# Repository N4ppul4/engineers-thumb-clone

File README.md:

# engineers-thumb-clone
Compression guitar pedal clone

Just my take on the popular compression pedal, its designed to use with perfboard.
This is not in any means verified or anything so take it with a grain of salt.
Program used for schematics and pcb layout is KiCad

Dont know much about copyrights so I assume its same as original design

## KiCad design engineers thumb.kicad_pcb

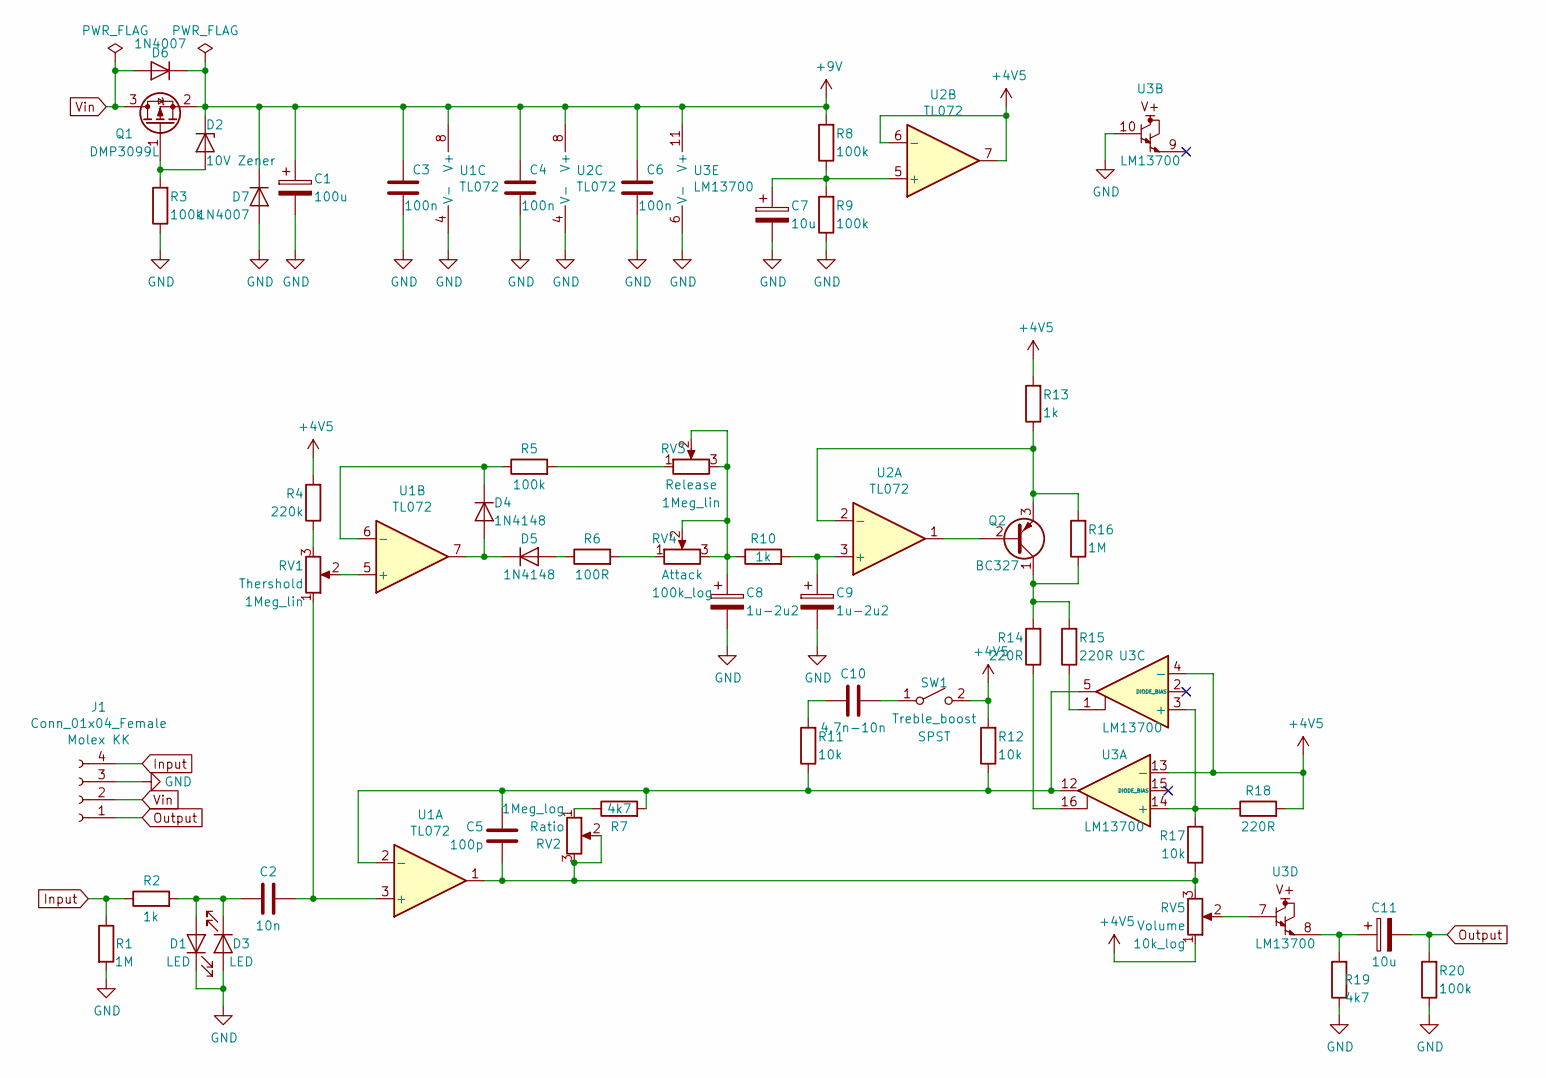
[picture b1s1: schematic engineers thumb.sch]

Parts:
C1: 100u; CP_Radial_D6.3mm_P2.50mm
C2: 10n; C_Box_P5.08mm
C3, C4, C6: 100n; C_Box_P5.08mm
C5: 100p; C_Disc_P2.50mm
C7, C11: 10u; CP_Radial_D6.3mm_P2.50mm
C8, C9: 1u-2u2; CP_Radial_D6.3mm_P2.50mm
C10: 4.7n-10n; C_Box_P5.08mm
D1, D3: LED; LED_D3.0mm
D2: 10V Zener; D_DO-35_SOD27_P7.62mm_Horizontal
D4, D5: 1N4148; D_DO-35_SOD27_P7.62mm_Horizontal
D6, D7: 1N4007; D_DO-35_SOD27_P7.62mm_Horizontal
J1: Conn_01x04_Female; Molex_KK-254_01x04_P2.54mm_Right_Angle
Q1: DMP3099L; SOT-23W_Handsoldering
Q2: BC327; TO-92_Inline_Wide
R1, R16: 1M; R_Axial_DIN0204_L3.6mm_D1.6mm_P7.62mm_Horizontal
R2, R10, R13: 1k; R_Axial_DIN0204_L3.6mm_D1.6mm_P7.62mm_Horizontal
R3, R5, R8, R9, R20: 100k; R_Axial_DIN0204_L3.6mm_D1.6mm_P7.62mm_Horizontal
R4: 220k; R_Axial_DIN0204_L3.6mm_D1.6mm_P7.62mm_Horizontal
R6: 100R; R_Axial_DIN0204_L3.6mm_D1.6mm_P7.62mm_Horizontal
R7, R19: 4k7; R_Axial_DIN0204_L3.6mm_D1.6mm_P7.62mm_Horizontal
R11, R12, R17: 10k; R_Axial_DIN0204_L3.6mm_D1.6mm_P7.62mm_Horizontal
R14, R15, R18: 220R; R_Axial_DIN0204_L3.6mm_D1.6mm_P7.62mm_Horizontal
RV1, RV3: 1Meg_lin; Alpha_16mm_potentiometer
RV2: 1Meg_log; Alpha_16mm_potentiometer
RV4: 100k_log; Alpha_16mm_potentiometer
RV5: 10k_log; Alpha_16mm_potentiometer
SW1: SPST; PinSocket_2x01_P2.54mm_Vertical_Wide
U1, U2: TL072; DIP-8_Socket
U3: LM13700; DIP-16_Socket

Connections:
+4V5: R4.2, R12.2, R13.2, R18.2, RV5.1, SW1.2 (B), U2.6 (-), U2.7, U3.4 (-), U3.13 (-)
+9V: C1.1, C3.1, C4.1, C6.1, D2.1 (K), D6.1 (K), D7.1 (K), Q1.2 (S), R8.2, U1.8 (V+), U2.8 (V+), U3.11 (V+)
GND: C1.2, C3.2, C4.2, C6.2, C7.2, C8.2, C9.2, D1.1 (K), D3.2 (A), D7.2 (A), J1.3, R1.2, R3.1, R9.1, R19.1, R20.1, U1.4 (V-), U2.4 (V-), U3.6 (V-), U3.10
Input: J1.4, R1.1, R2.1
unnamed: C2.1, RV1.1, U1.3 (+)
unnamed: C2.2, D1.2 (A), D3.1 (K), R2.2
unnamed: C5.1, R7.2, R11.1, R12.1, U1.2 (-), U3.5, U3.12
unnamed: C5.2, R17.1, RV2.2, RV2.3, RV5.3, U1.1
unnamed: C7.1, R8.1, R9.2, U2.5 (+)
unnamed: C8.1, R10.1, RV3.2, RV3.3, RV4.2, RV4.3
unnamed: C9.1, R10.2, U2.3 (+)
unnamed: C10.1, SW1.1 (A)
unnamed: C10.2, R11.2
unnamed: C11.1, R19.2, U3.8
unnamed: D2.2 (A), Q1.1 (G), R3.2
unnamed: D4.1 (K), R5.1, U1.6 (-)
unnamed: D4.2 (A), D5.1 (K), U1.7
unnamed: D5.2 (A), R6.1
unnamed: Q2.1 (C), R14.2, R15.2, R16.1
unnamed: Q2.2 (B), U2.1
unnamed: Q2.3 (E), R13.1, R16.2, U2.2 (-)
unnamed: R4.1, RV1.3
unnamed: R5.2, RV3.1
unnamed: R6.2, RV4.1
unnamed: R7.1, RV2.1
unnamed: R14.1, U3.16
unnamed: R15.1, U3.1
unnamed: R17.2, R18.1, U3.3 (+), U3.14 (+)
unnamed: RV1.2, U1.5 (+)
unnamed: RV5.2, U3.7
Output: C11.2, J1.1, R20.2
Vin: D6.2 (A), J1.2, Q1.3 (D)

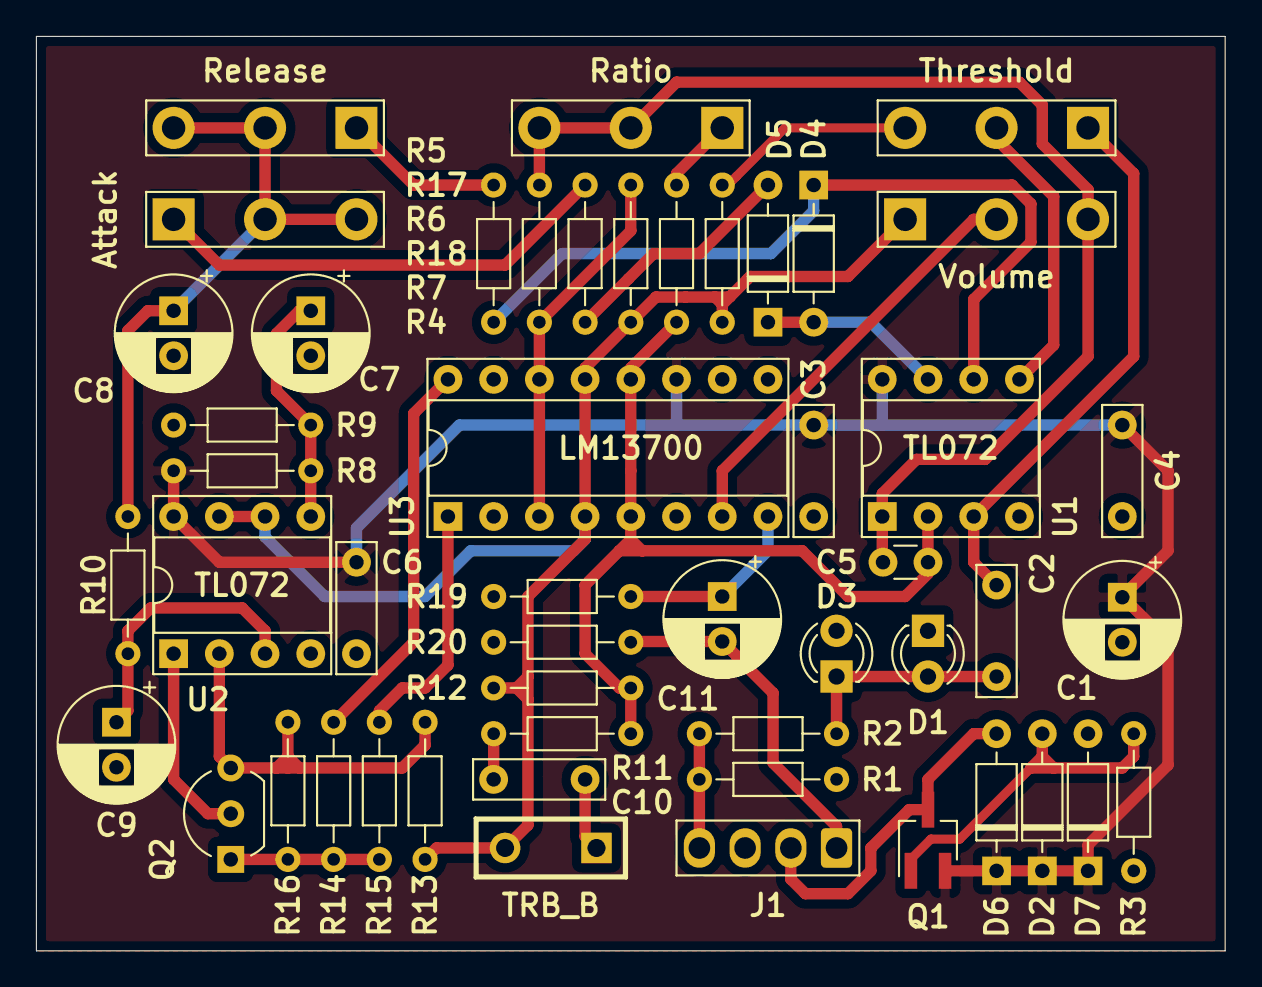
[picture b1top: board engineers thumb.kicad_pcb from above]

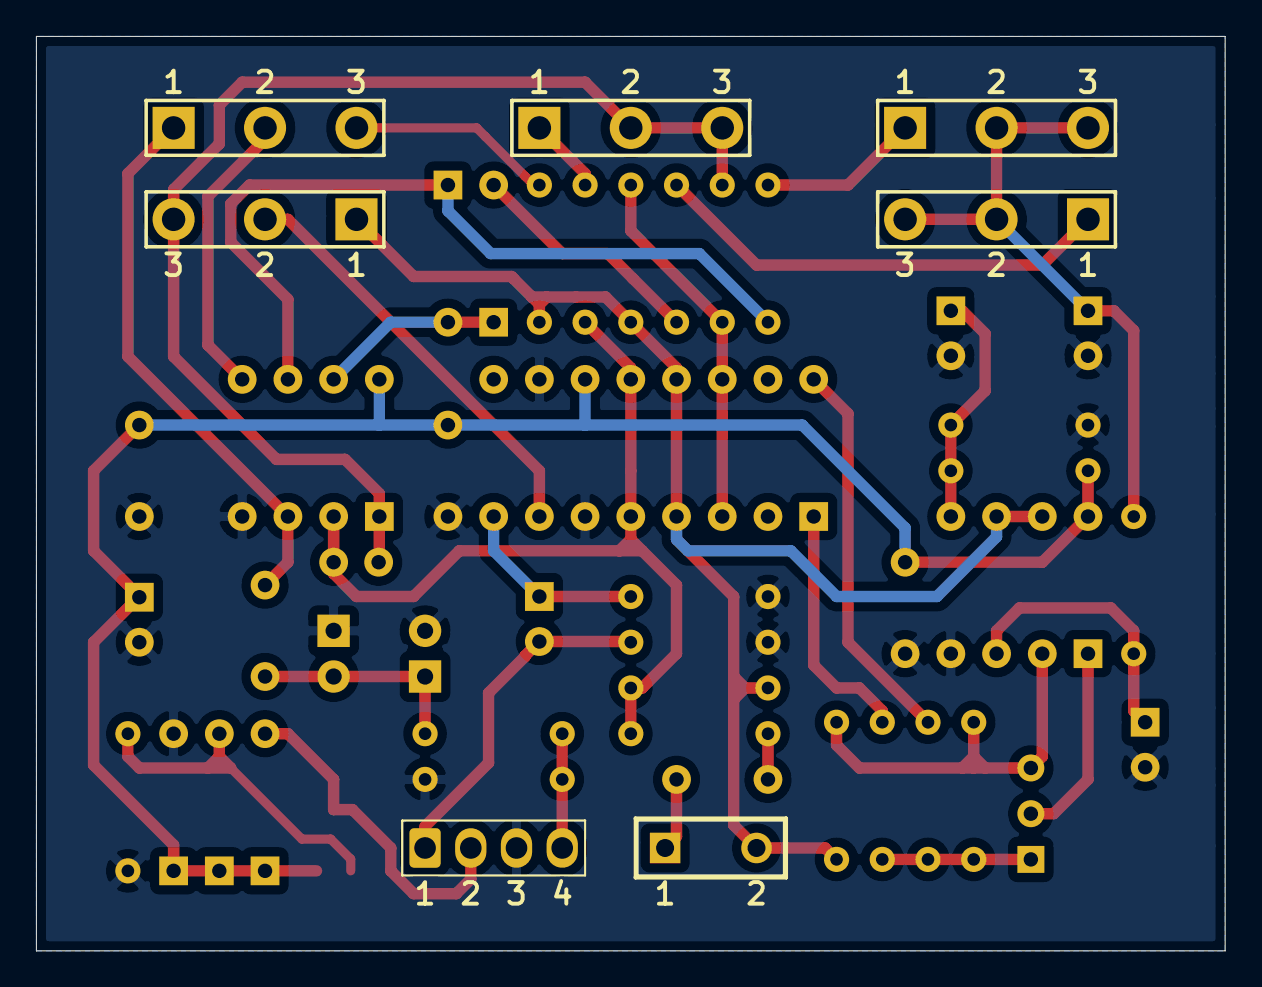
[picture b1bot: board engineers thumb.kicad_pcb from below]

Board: 2 copper layers, 66.0 x 50.8 mm, 50 parts (6 on the bottom side), 32 nets.

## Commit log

2020-03-11 First Commits
2020-03-11 Corrected footprints
2020-03-18 updated layout
2020-04-05 added capacitor
2020-04-22 Starting to do changes
2020-04-24 Almost done
2020-04-25 Finnished?
2020-04-28 Its never done
2020-05-19 Good progress made
